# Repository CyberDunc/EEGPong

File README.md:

# EEGPong
Arduino and Visual studio code necessary to play EEG Pong
Arduino zero code takes input through Analog0 input pin and communicates with computer over usb through program pin
Visual studio code needs opengl and several other libraries: glad , glfw3 , fftw3 , stdio , stdlib . 
The Visual studio code should be started after the Arduino is running
I used Ag/AgCl sintered electrodes and elecectrode gel, however an inexpensive alternative are gold electrodes, four are preffered but it can be used with 3 if you leave one of the biases unconnected. Aloe vera is a possible substitute for eeg gel, however you only need a small amount of gel and it is relatively cheap. 
The board designs were done in Eagle and assembled in house at my university, however PCBworld is my preffered manufacturer otherwise.

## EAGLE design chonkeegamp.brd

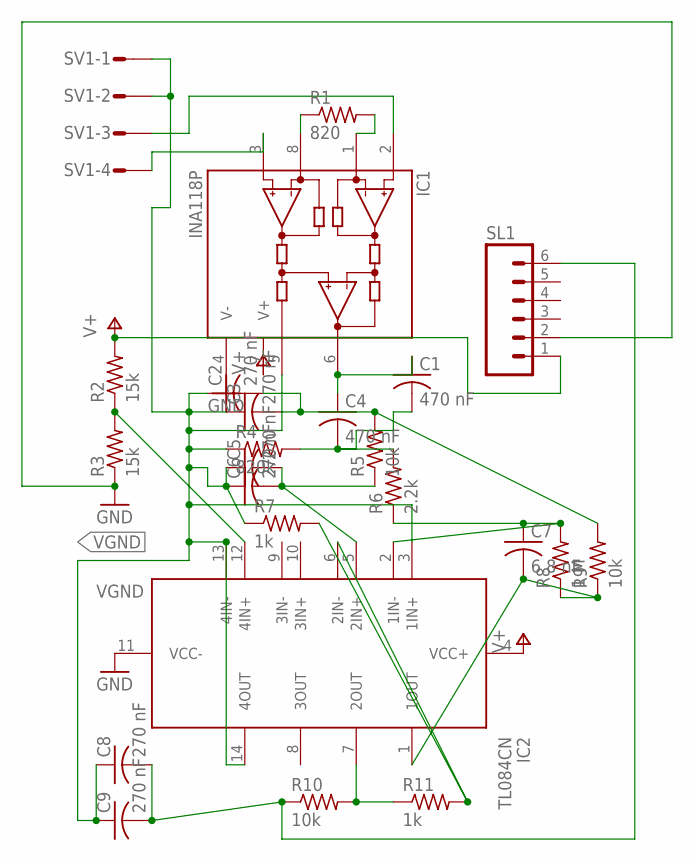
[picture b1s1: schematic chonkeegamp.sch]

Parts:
C1, C4: 470 nF; C050-024X044; MPN BFC237390043
C2, C3, C5, C6, C8, C9: 270 nF; C050-024X044; MPN BFC237390132
C7: 6.8 nF; C050-024X044; MPN C315C682K1R5TA
IC1: INA118P; DIL08
IC2: TL084CN; DIP794W53P254L1930H508Q14N; MPN TL084CN
R1: 820; 0207/7; MPN MCF 0.5W 820R
R2, R3: 15k; 0207/7; MPN MCF 1W 15K
R4: 820k; 0207/7; MPN MCF 0.25W 820K
R5, R9, R10: 10k; 0207/7; MPN MCCFR0W4J0103A50
R6: 2.2k; 0207/7; MPN MCF 0.5W 2K2
R7, R11: 1k; 0207/7; MPN MCCFR0S2J0102A20
R8: 1 M; 0207/7; MPN MCF 0.5W 1M
SL1: M06; 06P
SV1: L04P

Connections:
GND: IC1.4 (V-), IC2.11 (VCC-), R3.1, SL1.2
unnamed: C1.1, C4.1, IC1.6 (OUT)
unnamed: C1.2, C4.2, R4.2, R6.2
unnamed: C7.1, IC2.2 (1IN-), R6.1, R8.2
unnamed: C7.2, IC2.1 (1OUT), R8.1, R9.1
unnamed: C2.2, C3.2, R5.2, R9.2
unnamed: C5.2, C6.2, IC2.5 (2IN+), R5.1
unnamed: IC1.3 (+IN), SV1.4
unnamed: IC2.6 (2IN-), R7.2, R11.2
unnamed: IC2.7 (2OUT), R10.2, R11.1
unnamed: C8.2, C9.2, R10.1, SL1.6
unnamed: IC2.12 (4IN+), R2.1, R3.2
unnamed: IC1.2 (-IN), SV1.3
unnamed: IC1.1 (RG), R1.2
unnamed: IC1.8 (RG), R1.1
V+: IC1.7 (V+), IC2.4 (VCC+), R2.2, SL1.1
VGND: C2.1, C3.1, C5.1, C6.1, C8.1, C9.1, IC1.5 (REF), IC2.3 (1IN+), IC2.13 (4IN-), IC2.14 (4OUT), R4.1, R7.1, SV1.1, SV1.2

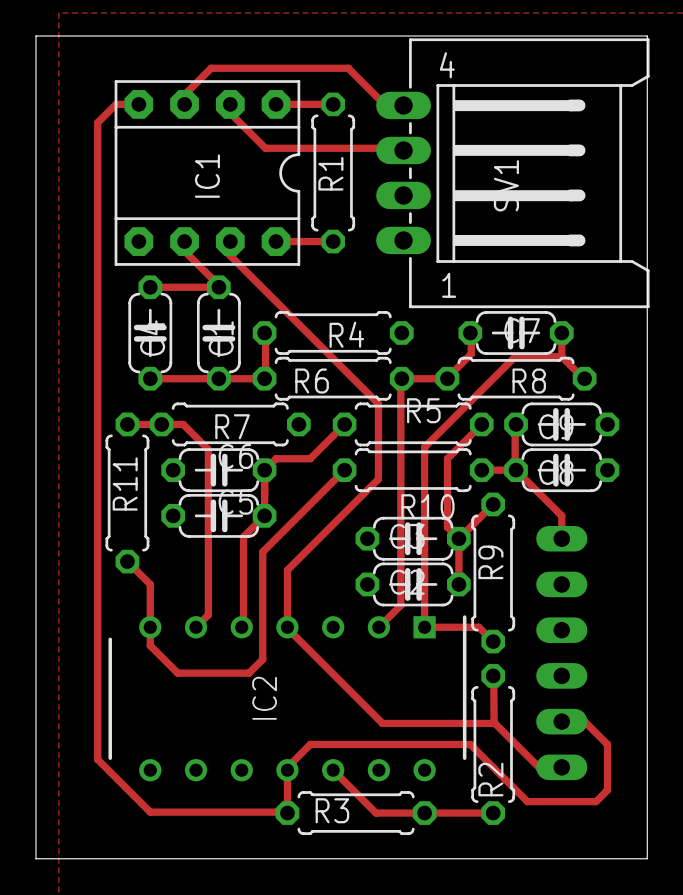
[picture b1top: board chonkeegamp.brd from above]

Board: 2 copper layers, 34.0 x 45.7 mm, 24 parts (1 on the bottom side), 17 nets.
